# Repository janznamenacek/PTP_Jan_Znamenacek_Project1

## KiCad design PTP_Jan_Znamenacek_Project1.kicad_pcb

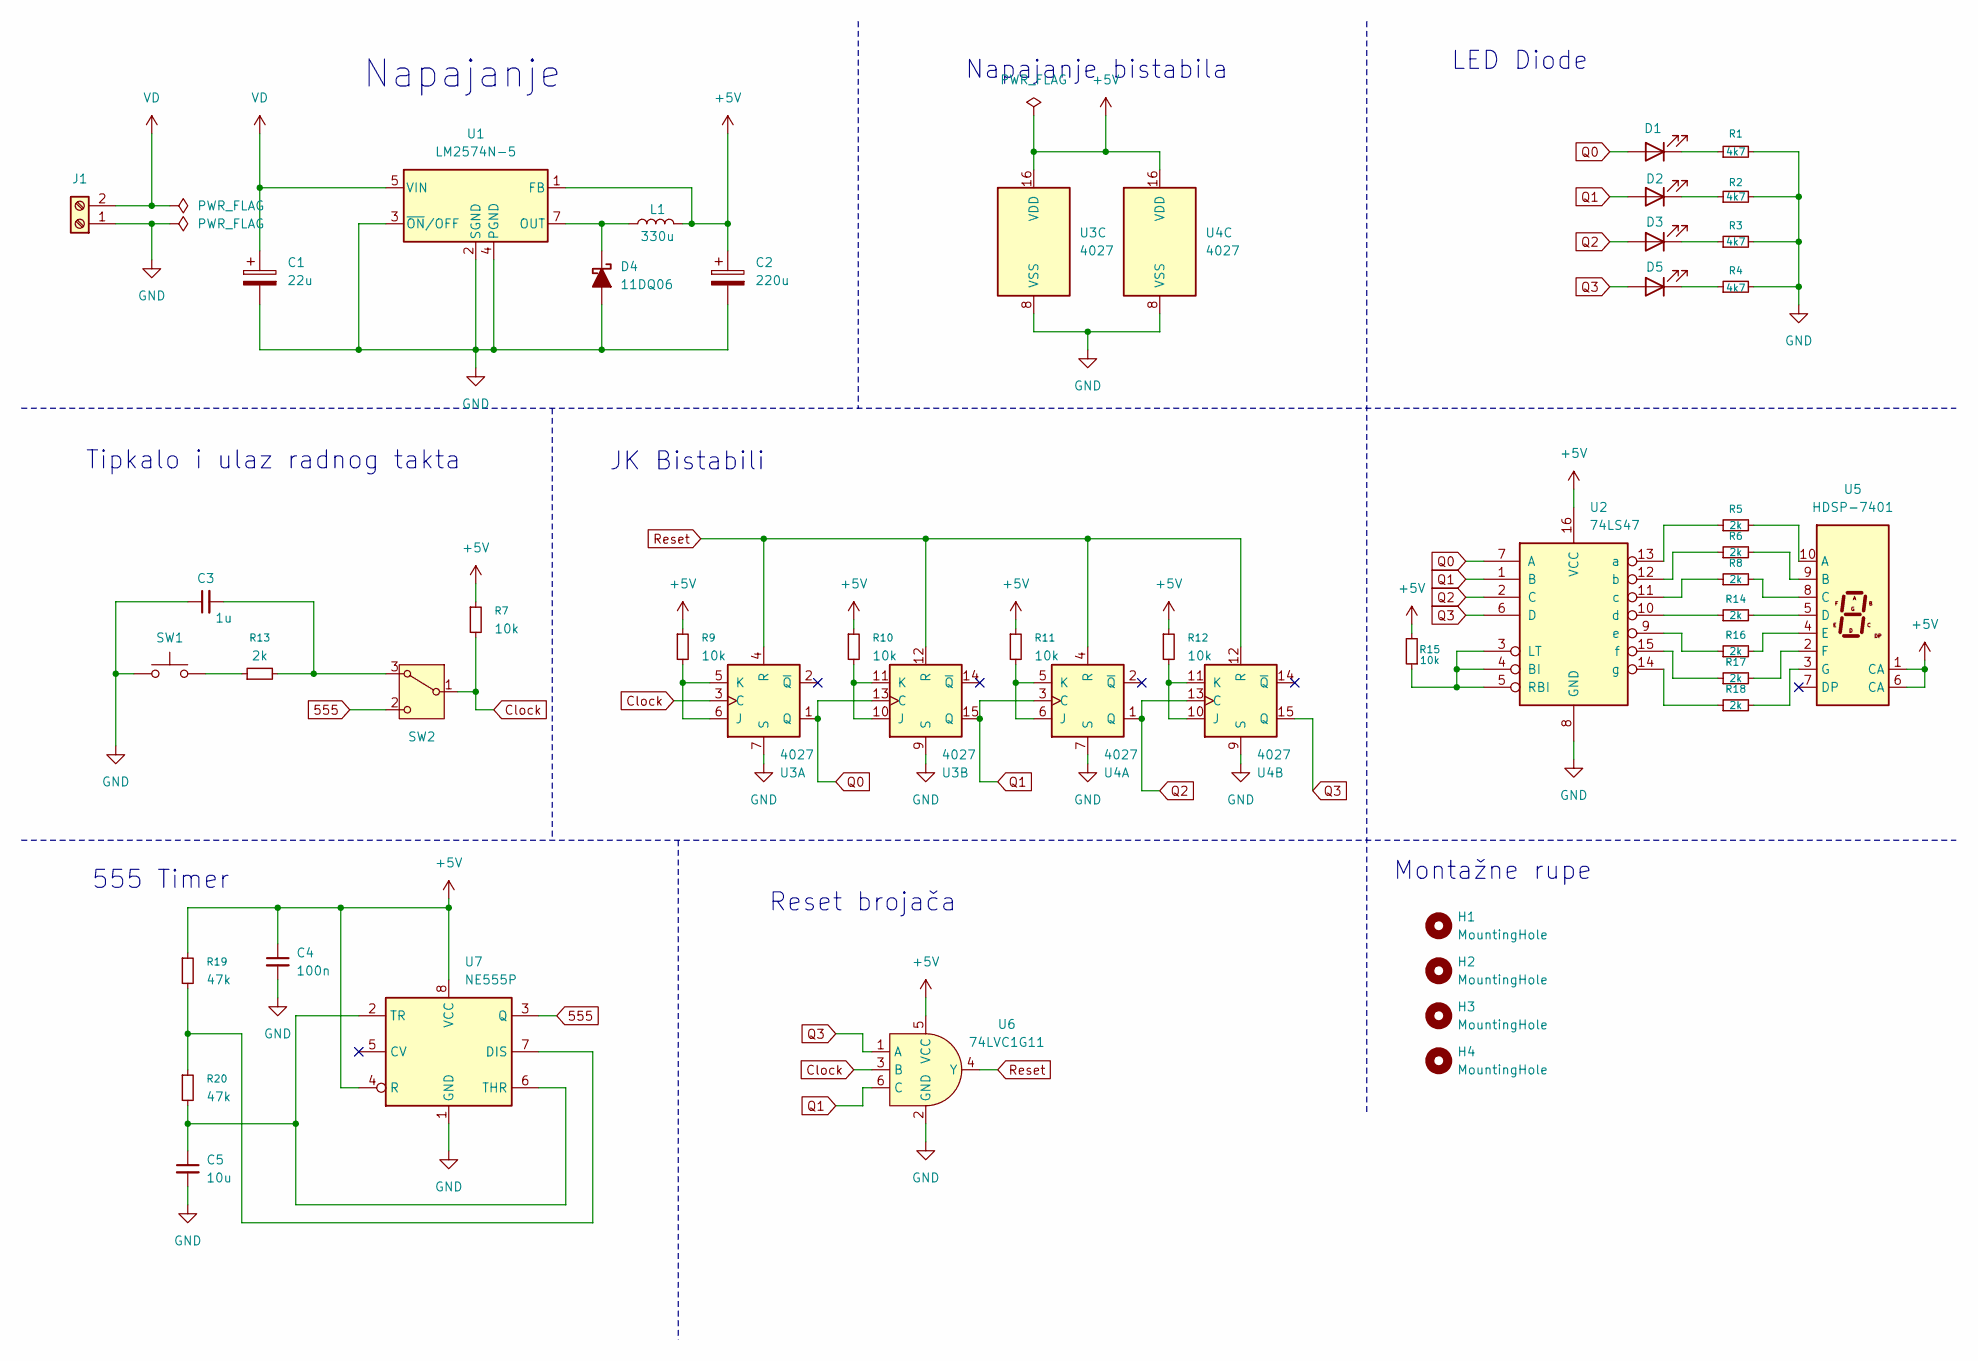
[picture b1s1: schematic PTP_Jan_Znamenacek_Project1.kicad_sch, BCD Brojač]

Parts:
C1: 22u; CP_Radial_D5.0mm_P2.00mm; Manufacturer Part Number EWH1EM220D11OT
C2: 220u; CP_Radial_D5.0mm_P2.00mm; Manufacturer Part Number RD1A227M05011BB
C3: 1u; C_1206_3216Metric_Pad1.33x1.80mm_HandSolder; Manufacturer Part Number CL31B105KBHNNNE
C4: 100n; C_1206_3216Metric_Pad1.33x1.80mm_HandSolder; Manufacturer Part Number CL31B104KBCNNNC
C5: 10u; C_1206_3216Metric_Pad1.33x1.80mm_HandSolder; Manufacturer Part Number CL31A106KBHNNNE
D1, D2, D3, D5: LED; LED_D5.0mm
D4: 11DQ06; D_DO-41_SOD81_P12.70mm_Horizontal; Manufacturer Part Number 11DQ06TA
H1, H2, H3, H4: MountingHole; MountingHole_5.5mm
J1: Screw_Terminal_01x02; TerminalBlock_MetzConnect_Type011_RT05502HBLC_1x02_P5.00mm_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; Manufacturer Part Number DG301-5.0-02P-12-00A(H)
L1: 330u; L_Radial_D7.2mm_P3.00mm_Murata_1700; Manufacturer Part Number COIL0608-0.33
R1, R2, R3, R4: 4k7; R_Axial_DIN0207_L6.3mm_D2.5mm_P10.16mm_Horizontal
R5, R6, R8, R13, R14, R16, R17, R18: 2k; R_1206_3216Metric_Pad1.30x1.75mm_HandSolder
R7, R9, R10, R11, R12, R15: 10k; R_1206_3216Metric_Pad1.30x1.75mm_HandSolder
R19, R20: 47k; R_1206_3216Metric_Pad1.30x1.75mm_HandSolder
SW1: SW_PUSH_6mm_H4.3mm
SW2: SW_Slide_SPDT_Straight_CK_OS102011MS2Q
U1: LM2574N-5; DIP-8_W7.62mm
U2: 74LS47; DIP-16_W7.62mm_Socket_LongPads
U3, U4: 4027; DIP-16_W7.62mm_Socket_LongPads
U5: HDSP-7401
U6: 74LVC1G11; SOT-23-6
U7: NE555P; DIP-8_W7.62mm

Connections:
555: SW2.2 (C), U7.3 (Q)
+5V: C2.1, C4.1, L1.2, R7.1, R9.1, R10.1, R11.1, R12.1, R15.2, R19.1, U1.1 (FB), U2.16 (VCC), U3.16 (VDD), U4.16 (VDD), U5.1 (CA), U5.6 (CA), U6.5 (VCC), U7.4 (R), U7.8 (VCC)
Clock: R7.2, SW2.1 (B), U3.3 (C), U6.3 (B)
GND: C1.2, C2.2, C3.1, C4.2, C5.2, D4.2 (A), J1.1, R1.2, R2.2, R3.2, R4.2, SW1.1, U1.2 (SGND), U1.3 (~ON/OFF), U1.4 (PGND), U2.8 (GND), U3.7 (S), U3.8 (VSS), U3.9 (S), U4.7 (S), U4.8 (VSS), U4.9 (S), U6.2 (GND), U7.1 (GND)
unnamed: D1.1 (K), R1.1
unnamed: D2.1 (K), R2.1
unnamed: D3.1 (K), R3.1
unnamed: D4.1 (K), L1.1, U1.7 (OUT)
unnamed: D5.1 (K), R4.1
unnamed: R13.1, SW1.2
unnamed: C3.2, R13.2, SW2.3 (A)
unnamed: R15.1, U2.3 (LT), U2.4 (BI), U2.5 (RBI)
unnamed: R5.1, U2.13 (a)
unnamed: R6.1, U2.12 (b)
unnamed: R8.1, U2.11 (c)
unnamed: R14.1, U2.10 (d)
unnamed: R16.1, U2.9 (e)
unnamed: R17.1, U2.15 (f)
unnamed: R18.1, U2.14 (g)
unnamed: R9.2, U3.5 (K), U3.6 (J)
unnamed: R10.2, U3.10 (J), U3.11 (K)
unnamed: R11.2, U4.5 (K), U4.6 (J)
unnamed: R12.2, U4.10 (J), U4.11 (K)
unnamed: R5.2, U5.10 (A)
unnamed: R6.2, U5.9 (B)
unnamed: R8.2, U5.8 (C)
unnamed: R14.2, U5.5 (D)
unnamed: R16.2, U5.4 (E)
unnamed: R17.2, U5.2 (F)
unnamed: R18.2, U5.3 (G)
unnamed: R19.2, R20.1, U7.7 (DIS)
unnamed: C5.1, R20.2, U7.2 (TR), U7.6 (THR)
Q0: D1.2 (A), U2.7 (A), U3.1 (Q), U3.13 (C)
Q1: D2.2 (A), U2.1 (B), U3.15 (Q), U4.3 (C), U6.6 (C)
Q2: D3.2 (A), U2.2 (C), U4.1 (Q), U4.13 (C)
Q3: D5.2 (A), U2.6 (D), U4.15 (Q), U6.1 (A)
Reset: U3.4 (R), U3.12 (R), U4.4 (R), U4.12 (R), U6.4 (Y)
VD: C1.1, J1.2, U1.5 (VIN)

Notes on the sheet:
JK Bistabili
Reset brojača
Napajanje
555 Timer
Tipkalo i ulaz radnog takta
Montažne rupe
Napajanje bistabila
LED Diode

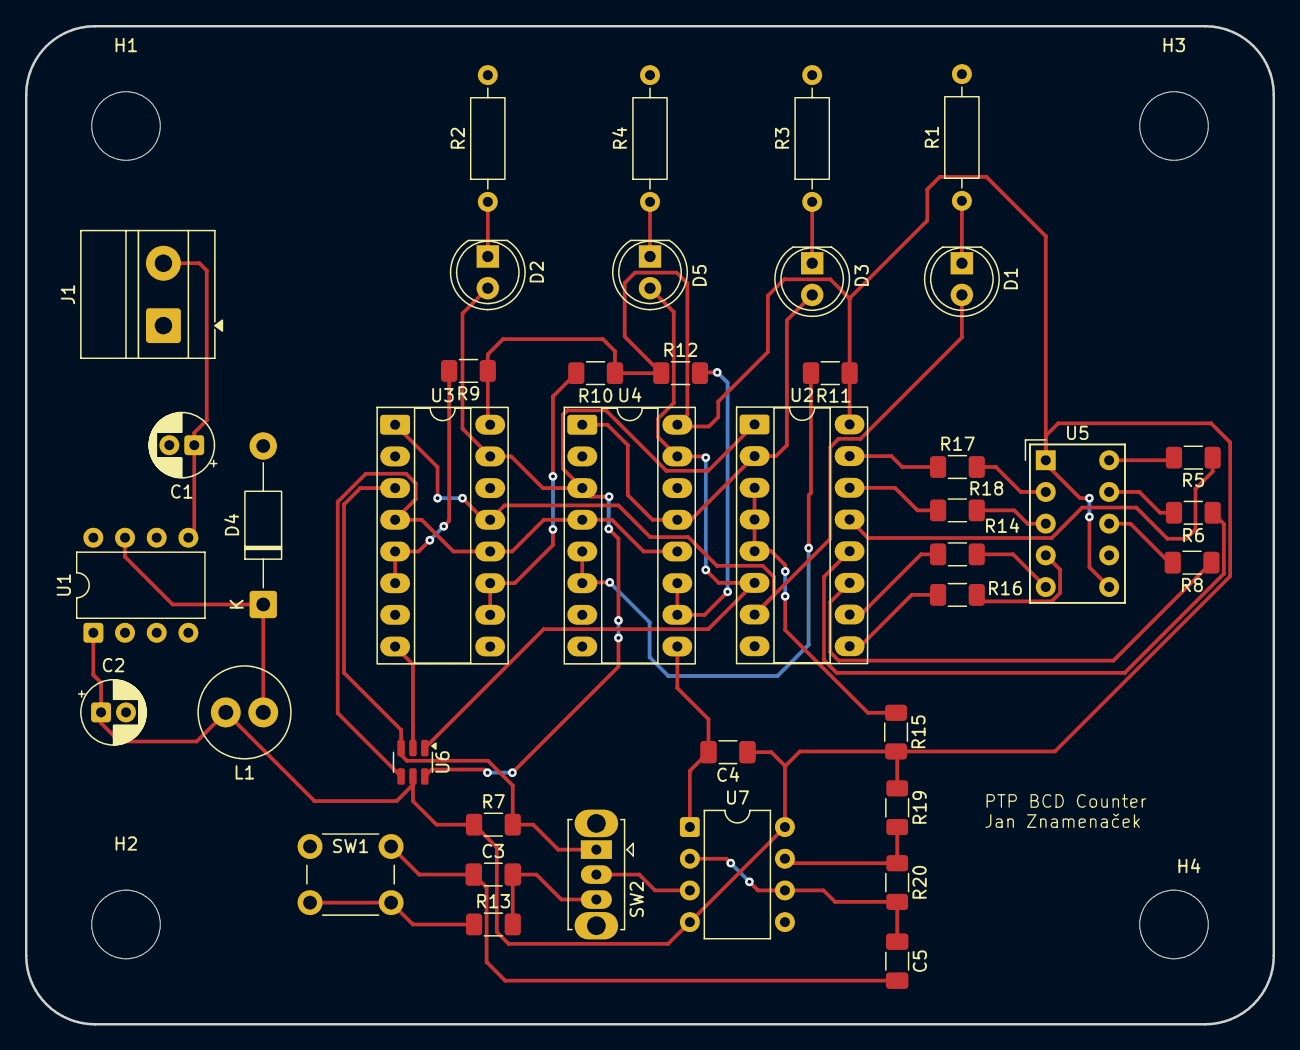
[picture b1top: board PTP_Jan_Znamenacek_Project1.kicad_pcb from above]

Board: 2 copper layers, 100.0 x 80.0 mm, 45 parts (0 on the bottom side), 38 nets.

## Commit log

2025-10-21 Ispunjena sastavnica
2025-10-28 Dodan NE555P
2025-11-04 Footprint i simbol
2025-11-11 LV_4
2025-11-25 PCB Pocetak
2025-12-09 PCB Crtanje
2025-12-16 Gerberi
